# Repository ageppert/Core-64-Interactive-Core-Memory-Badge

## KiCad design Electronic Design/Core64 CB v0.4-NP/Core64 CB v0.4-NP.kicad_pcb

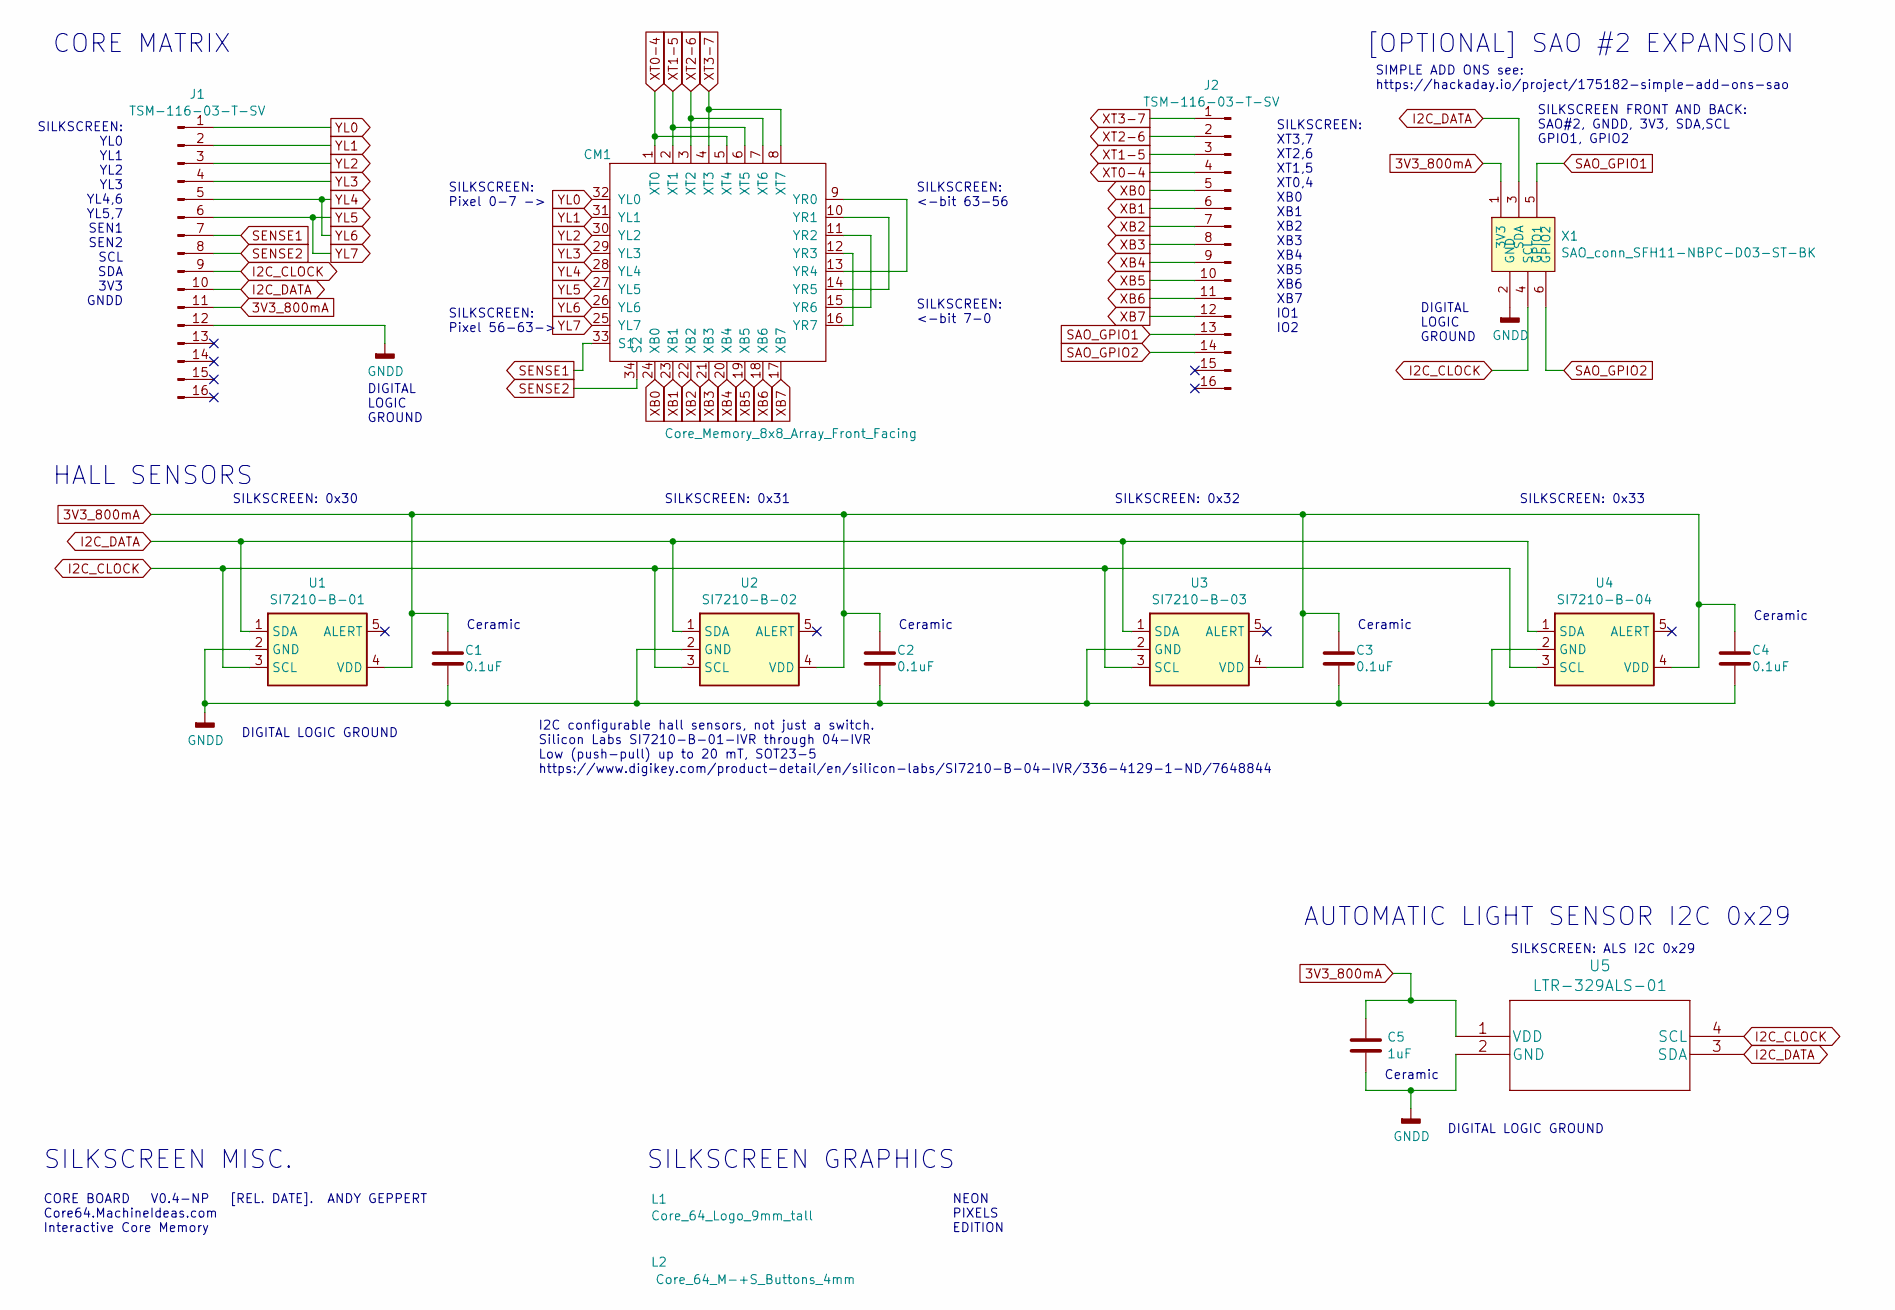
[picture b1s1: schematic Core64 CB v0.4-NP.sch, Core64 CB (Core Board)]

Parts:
C1, C2, C3, C4: 0.1uF; C_0805_2012Metric
C5: 1uF; C_0805_2012Metric
CM1: Core_Memory_8x8_Array_Front_Facing; core_64_0.3in_spacing_front_facing
J1, J2: TSM-116-03-T-SV‎; PinHeader_1x16_P2.54mm_Vertical
L1: Core_64_Logo_9mm_tall; Core64_Logo_9mm_tall
L2: Core_64_M-+S_Buttons_4mm; Core64-M_-_+_S_Buttons
U1: SI7210-B-01; SOT-23-5
U2: SI7210-B-02; SOT-23-5
U3: SI7210-B-03; SOT-23-5
U4: SI7210-B-04; SOT-23-5
U5: LTR-329ALS-01
X1: SAO_conn_SFH11-NBPC-D03-ST-BK; Badgelife-SAOv169-BADGE-2x3

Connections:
3V3_800mA: C1.1, C2.1, C3.1, C4.1, C5.1, J1.11, U1.4 (VDD), U2.4 (VDD), U3.4 (VDD), U4.4 (VDD), U5.1 (VDD), X1.1 (3V3)
GNDD: C1.2, C2.2, C3.2, C4.2, C5.2, J1.12, U1.2 (GND), U2.2 (GND), U3.2 (GND), U4.2 (GND), U5.2 (GND), X1.2 (GND)
I2C_CLOCK: J1.9, U1.3 (SCL), U2.3 (SCL), U3.3 (SCL), U4.3 (SCL), U5.4 (SCL), X1.4 (SCL)
I2C_DATA: J1.10, U1.1 (SDA), U2.1 (SDA), U3.1 (SDA), U4.1 (SDA), U5.3 (SDA), X1.3 (SDA)
unnamed: CM1.10 (YR1), CM1.14 (YR5)
unnamed: CM1.11 (YR2), CM1.15 (YR6)
unnamed: CM1.12 (YR3), CM1.16 (YR7)
unnamed: CM1.9 (YR0), CM1.13 (YR4)
SAO_GPIO1: J2.13, X1.5 (GPIO1)
SAO_GPIO2: J2.14, X1.6 (GPIO2)
SENSE1: CM1.33 (S1), J1.7
SENSE2: CM1.34 (S2), J1.8
XB0: CM1.24 (XB0), J2.5
XB1: CM1.23 (XB1), J2.6
XB2: CM1.22 (XB2), J2.7
XB3: CM1.21 (XB3), J2.8
XB4: CM1.20 (XB4), J2.9
XB5: CM1.19 (XB5), J2.10
XB6: CM1.18 (XB6), J2.11
XB7: CM1.17 (XB7), J2.12
XT0-4: CM1.1 (XT0), CM1.5 (XT4), J2.4
XT1-5: CM1.2 (XT1), CM1.6 (XT5), J2.3
XT2-6: CM1.3 (XT2), CM1.7 (XT6), J2.2
XT3-7: CM1.4 (XT3), CM1.8 (XT7), J2.1
YL0: CM1.32 (YL0), J1.1
YL1: CM1.31 (YL1), J1.2
YL2: CM1.30 (YL2), J1.3
YL3: CM1.29 (YL3), J1.4
YL4: CM1.26 (YL6), CM1.28 (YL4), J1.5
YL5: CM1.25 (YL7), CM1.27 (YL5), J1.6

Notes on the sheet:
SILKSCREEN: YL0 YL1 YL2 YL3 YL4,6 YL5,7 SEN1 SEN2 SCL SDA 3V3 GNDD
SILKSCREEN: XT3,7 XT2,6 XT1,5 XT0,4 XB0 XB1 XB2 XB3 XB4 XB5 XB6 XB7 IO1 IO2
DIGITAL LOGIC GROUND
I2C configurable hall sensors, not just a switch. Silicon Labs SI7210-B-01-IVR through 04-IVR Low (push-pull) up to 20 mT, SOT23-5 https://www.digikey.com/product-detail/en/silicon-labs/SI7210-B-04-IVR/336-4129-1-ND/7648844
DIGITAL LOGIC GROUND
SILKSCREEN: ALS I2C 0x29
SILKSCREEN FRONT AND BACK: SAO#2, GNDD, 3V3, SDA,SCL GPIO1, GPIO2
AUTOMATIC LIGHT SENSOR I2C 0x29
SILKSCREEN GRAPHICS
HALL SENSORS
CORE MATRIX
[OPTIONAL] SAO #2 EXPANSION
SILKSCREEN: 0x30
SILKSCREEN: 0x31
SILKSCREEN: 0x32
SILKSCREEN: 0x33
Ceramic
SILKSCREEN: Pixel 0-7 ->
SILKSCREEN: <-bit 63-56
SILKSCREEN: <-bit 7-0
SILKSCREEN: Pixel 56-63->
CORE BOARD V0.4-NP [REL. DATE]. ANDY GEPPERT Core64.MachineIdeas.com Interactive Core Memory
SILKSCREEN MISC.
NEON PIXELS EDITION
SIMPLE ADD ONS see: https://hackaday.io/project/175182-simple-add-ons-sao

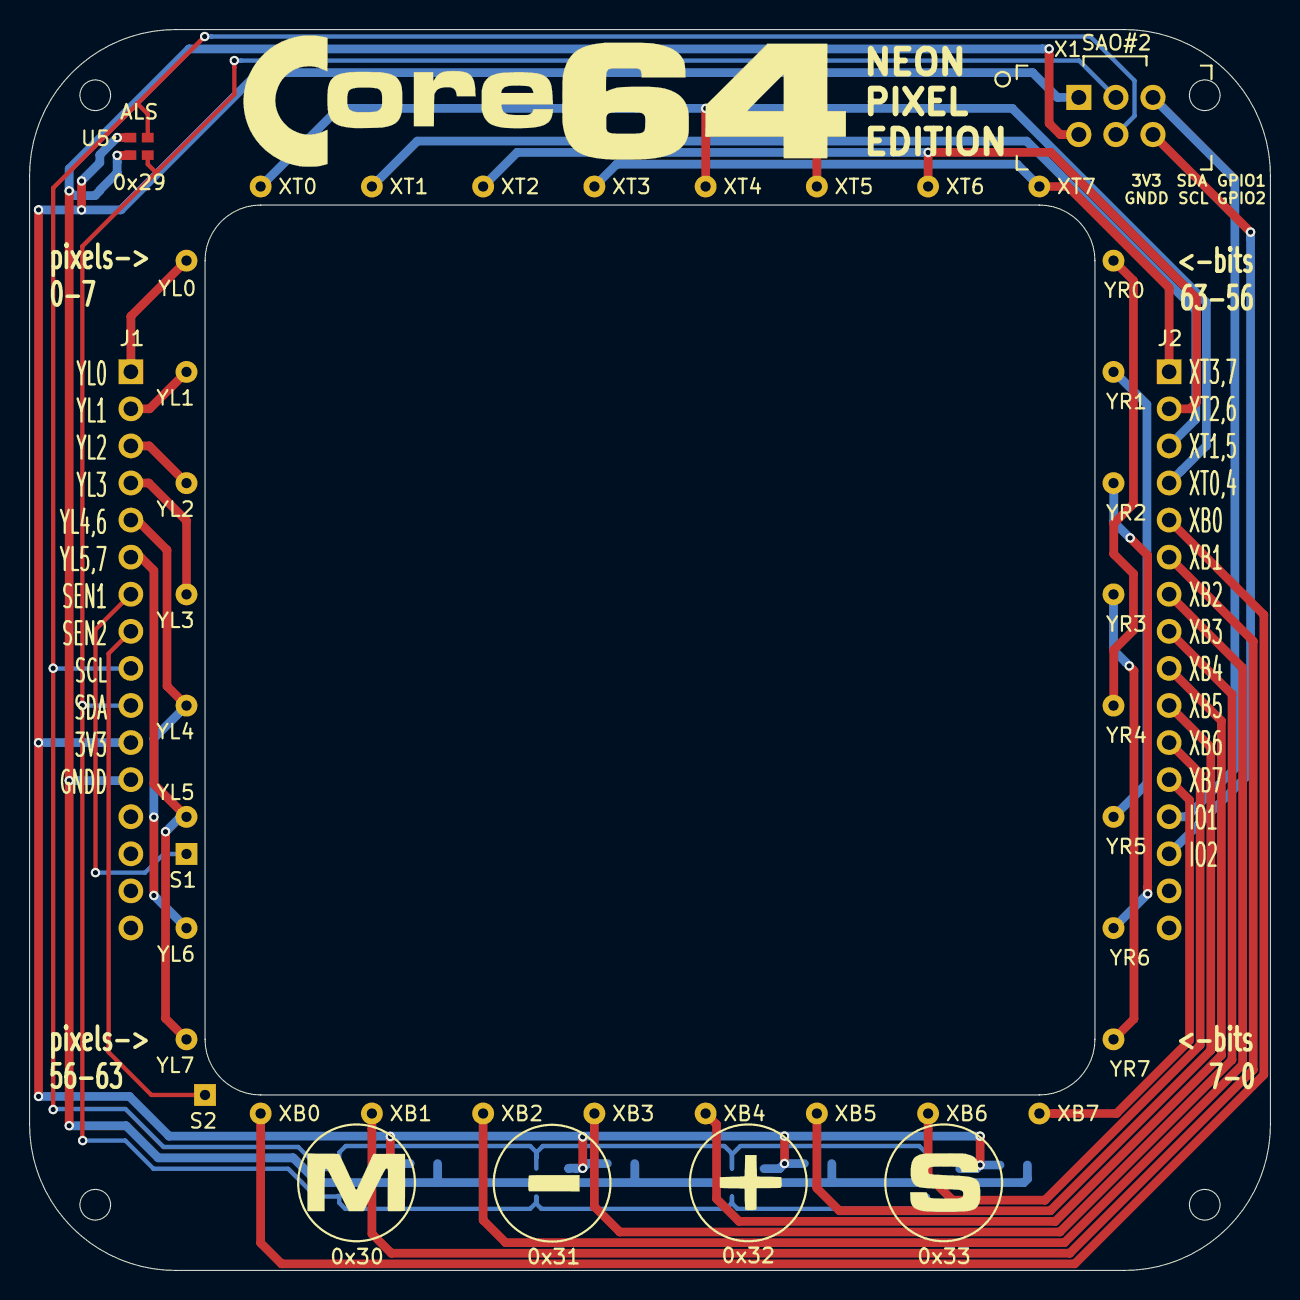
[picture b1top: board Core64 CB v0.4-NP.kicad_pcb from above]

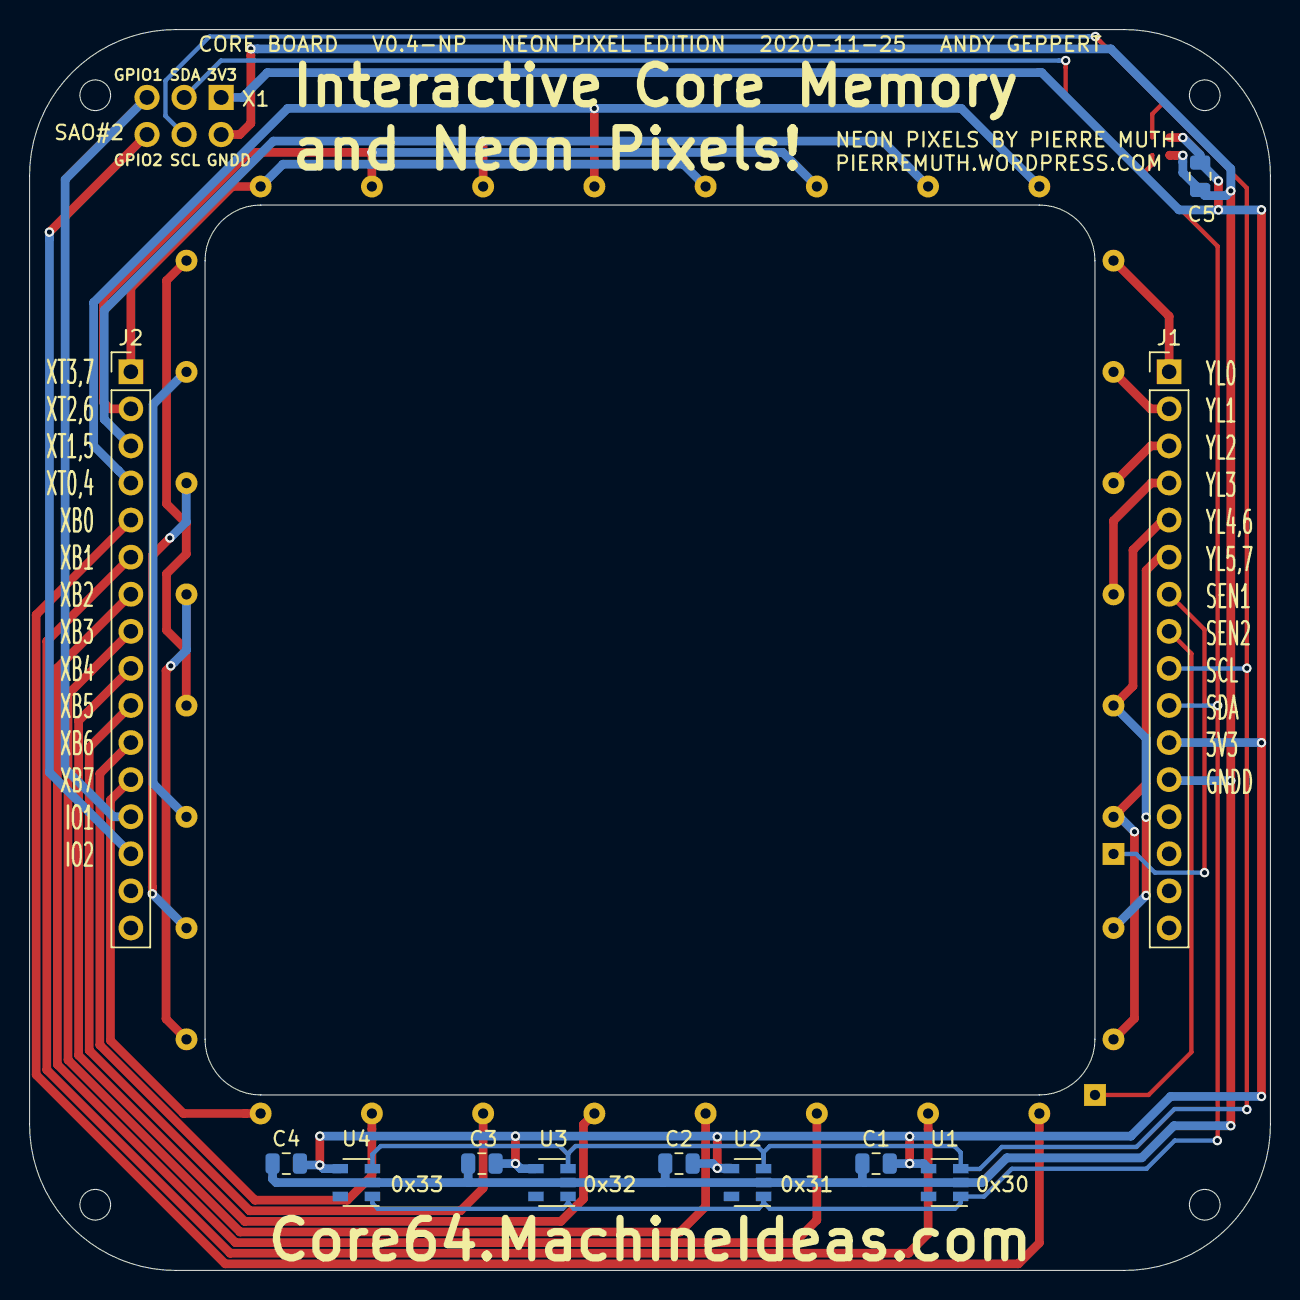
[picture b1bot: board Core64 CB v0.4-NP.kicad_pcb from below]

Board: 2 copper layers, 85.0 x 85.0 mm, 16 parts (11 on the bottom side), 30 nets.

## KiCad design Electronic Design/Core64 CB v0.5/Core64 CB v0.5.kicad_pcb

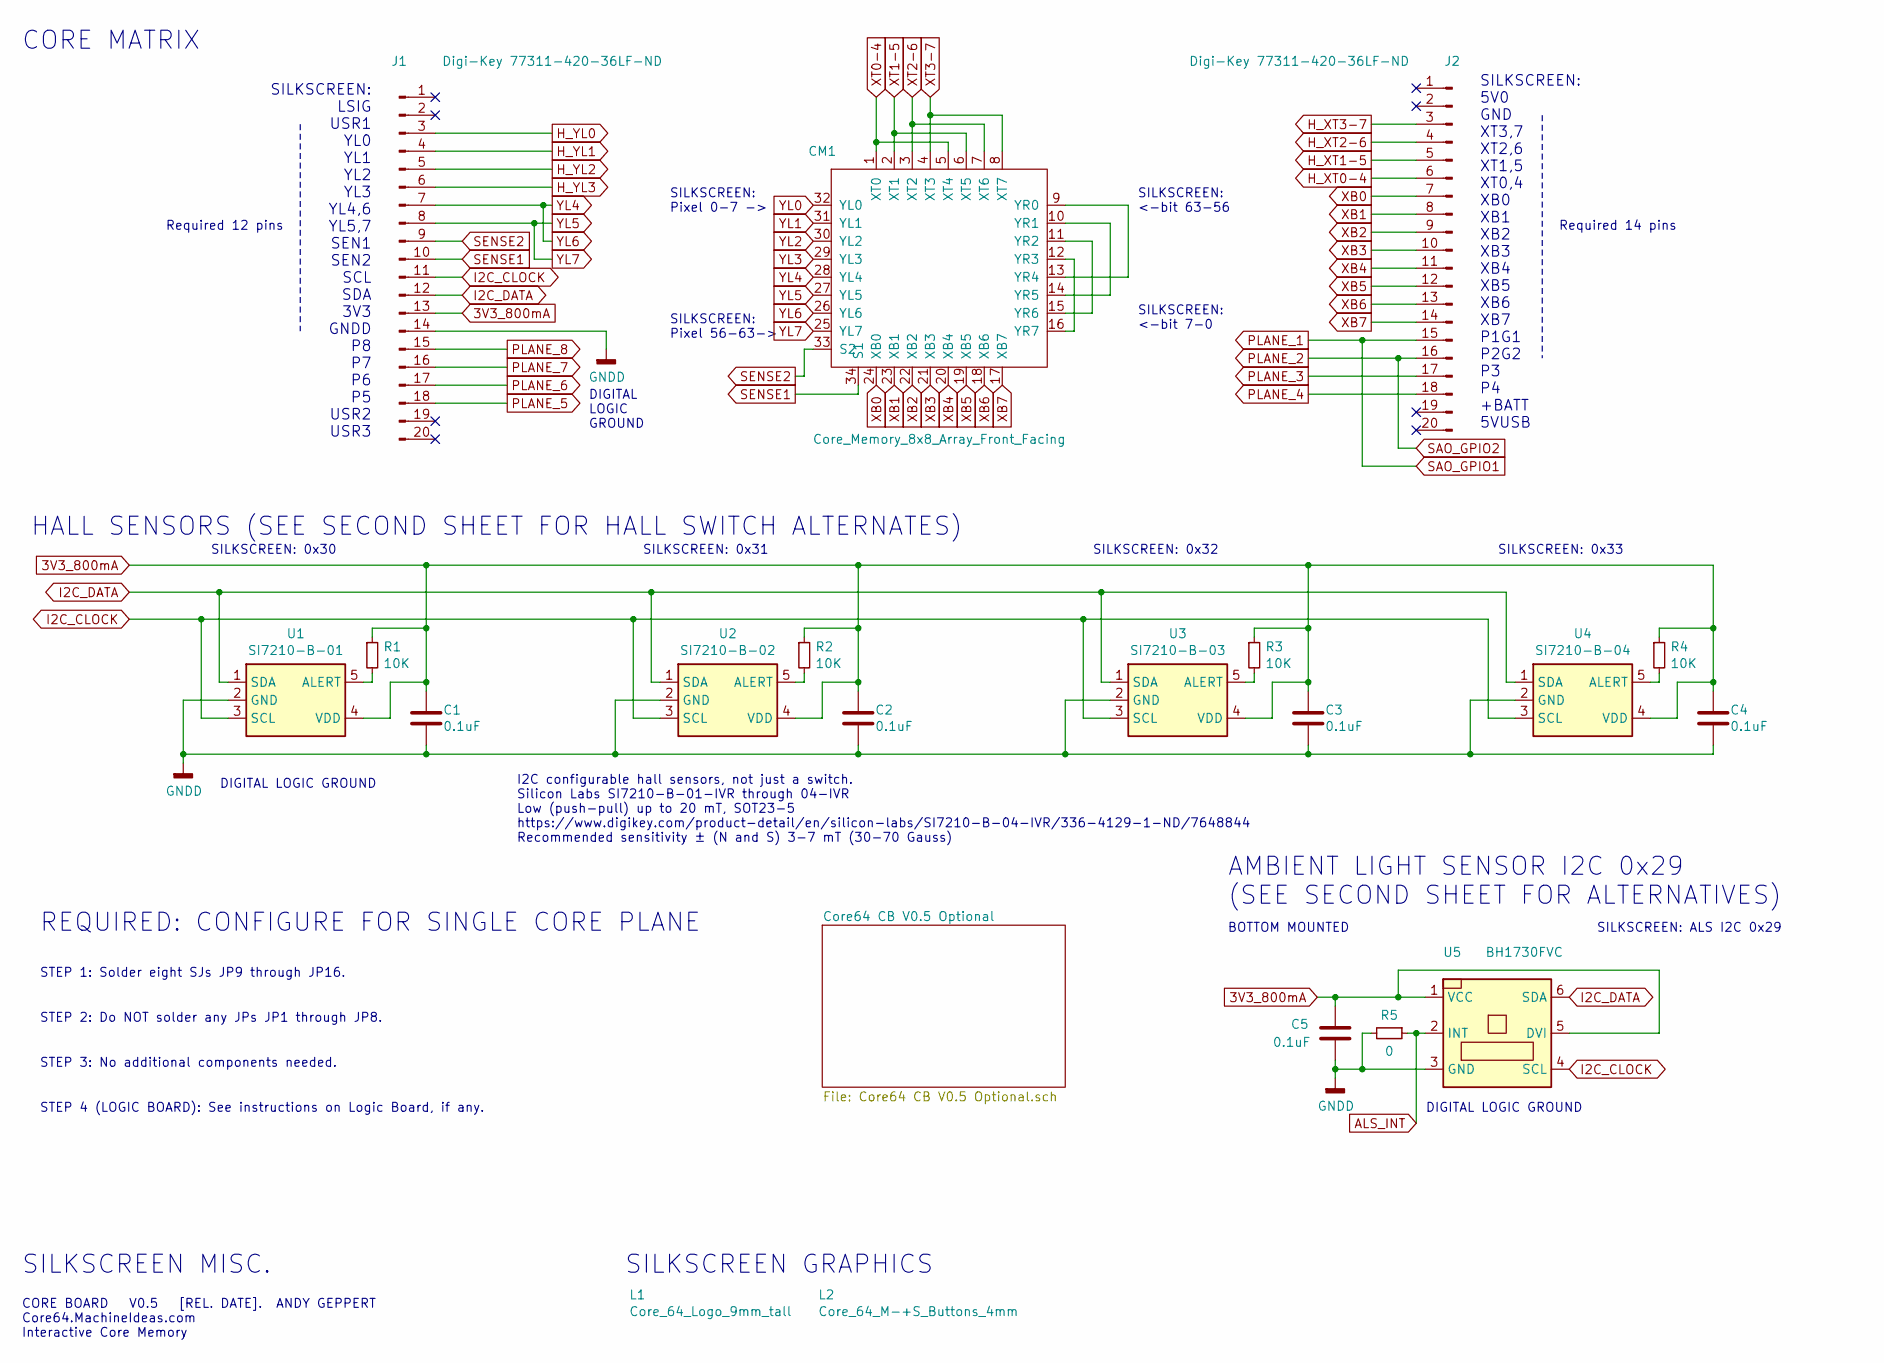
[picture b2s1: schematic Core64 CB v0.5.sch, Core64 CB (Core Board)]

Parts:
C1, C2, C3, C4, C5: 0.1uF; C_0805_2012Metric; LCSC C396718
CM1: Core_Memory_8x8_Array_Front_Facing; core_64_6.75mm_square_v0.5_front_facing
J1, J2: Digi-Key 77311-420-36LF-ND; PinHeader_1x20_P2.54mm_Vertical_SMD_and_TH_Pin1Right
L1: Core_64_Logo_9mm_tall; Core64_Logo_9mm_tall
L2: Core_64_M-+S_Buttons_4mm; Core64-M_-_+_S_Buttons
R1, R2, R3, R4: 10K; R_0805_2012Metric; LCSC C269724
R5: 0; R_0805_2012Metric; LCSC C115306
U1: SI7210-B-01; SOT-23-5
U2: SI7210-B-02; SOT-23-5
U3: SI7210-B-03; SOT-23-5
U4: SI7210-B-04; SOT-23-5
U5: BH1730FVC; BH1730-backside; LCSC C79616

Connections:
3V3_800mA: C1.1, C2.1, C3.1, C4.1, C5.1, J1.13, R1.1, R2.1, R3.1, R4.1, U1.4 (VDD), U2.4 (VDD), U3.4 (VDD), U4.4 (VDD), U5.1 (VCC), U5.5 (DVI); also elsewhere on the board
ALS_INT: R5.1, U5.2 (INT); also elsewhere on the board
GNDD: C1.2, C2.2, C3.2, C4.2, C5.2, J1.14, R5.2, U1.2 (GND), U2.2 (GND), U3.2 (GND), U4.2 (GND), U5.3 (GND); also elsewhere on the board
H_XT0-4: J2.6; also elsewhere on the board
H_XT1-5: J2.5; also elsewhere on the board
H_XT2-6: J2.4; also elsewhere on the board
H_XT3-7: J2.3; also elsewhere on the board
H_YL0: J1.3; also elsewhere on the board
H_YL1: J1.4; also elsewhere on the board
H_YL2: J1.5; also elsewhere on the board
H_YL3: J1.6; also elsewhere on the board
I2C_CLOCK: J1.11, U1.3 (SCL), U2.3 (SCL), U3.3 (SCL), U4.3 (SCL), U5.4 (SCL); also elsewhere on the board
I2C_DATA: J1.12, U1.1 (SDA), U2.1 (SDA), U3.1 (SDA), U4.1 (SDA), U5.6 (SDA); also elsewhere on the board
unnamed: CM1.10 (YR1), CM1.14 (YR5)
unnamed: CM1.11 (YR2), CM1.15 (YR6)
unnamed: CM1.12 (YR3), CM1.16 (YR7)
unnamed: CM1.9 (YR0), CM1.13 (YR4)
unnamed: R1.2, U1.5 (ALERT)
unnamed: R2.2, U2.5 (ALERT)
unnamed: R3.2, U3.5 (ALERT)
unnamed: R4.2, U4.5 (ALERT)
PLANE_1: J2.15; also elsewhere on the board
PLANE_2: J2.16; also elsewhere on the board
PLANE_3: J2.17; also elsewhere on the board
PLANE_4: J2.18; also elsewhere on the board
PLANE_5: J1.18; also elsewhere on the board
PLANE_6: J1.17; also elsewhere on the board
PLANE_7: J1.16; also elsewhere on the board
PLANE_8: J1.15; also elsewhere on the board
SENSE1: CM1.34 (S1), J1.10
SENSE2: CM1.33 (S2), J1.9
XB0: CM1.24 (XB0), J2.7
XB1: CM1.23 (XB1), J2.8
XB2: CM1.22 (XB2), J2.9
XB3: CM1.21 (XB3), J2.10
XB4: CM1.20 (XB4), J2.11
XB5: CM1.19 (XB5), J2.12
XB6: CM1.18 (XB6), J2.13
XB7: CM1.17 (XB7), J2.14
XT0-4: CM1.1 (XT0), CM1.5 (XT4); also elsewhere on the board
XT1-5: CM1.2 (XT1), CM1.6 (XT5); also elsewhere on the board
XT2-6: CM1.3 (XT2), CM1.7 (XT6); also elsewhere on the board
XT3-7: CM1.4 (XT3), CM1.8 (XT7); also elsewhere on the board
YL0: CM1.32 (YL0); also elsewhere on the board
YL1: CM1.31 (YL1); also elsewhere on the board
YL2: CM1.30 (YL2); also elsewhere on the board
YL3: CM1.29 (YL3); also elsewhere on the board
YL4: CM1.26 (YL6), CM1.28 (YL4), J1.7
YL5: CM1.25 (YL7), CM1.27 (YL5), J1.8

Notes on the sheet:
SILKSCREEN: LSIG USR1 YL0 YL1 YL2 YL3 YL4,6 YL5,7 SEN1 SEN2 SCL SDA 3V3 GNDD P8 P7 P6 P5 USR2 USR3
DIGITAL LOGIC GROUND
I2C configurable hall sensors, not just a switch. Silicon Labs SI7210-B-01-IVR through 04-IVR Low (push-pull) up to 20 mT, SOT23-5 https://www.digikey.com/product-detail/en/silicon-labs/SI7210-B-04-IVR/336-4129-1-ND/7648844 Recommended sensitivity ± (N and S) 3-7 mT (30-70 Gauss)
DIGITAL LOGIC GROUND
SILKSCREEN: ALS I2C 0x29
AMBIENT LIGHT SENSOR I2C 0x29 (SEE SECOND SHEET FOR ALTERNATIVES)
SILKSCREEN GRAPHICS
HALL SENSORS (SEE SECOND SHEET FOR HALL SWITCH ALTERNATES)
CORE MATRIX
SILKSCREEN: 0x30
SILKSCREEN: 0x31
SILKSCREEN: 0x32
SILKSCREEN: 0x33
SILKSCREEN: Pixel 0-7 ->
SILKSCREEN: <-bit 63-56
SILKSCREEN: <-bit 7-0
SILKSCREEN: Pixel 56-63->
CORE BOARD V0.5 [REL. DATE]. ANDY GEPPERT Core64.MachineIdeas.com Interactive Core Memory
SILKSCREEN MISC.
REQUIRED: CONFIGURE FOR SINGLE CORE PLANE
STEP 1: Solder eight SJs JP9 through JP16.
STEP 2: Do NOT solder any JPs JP1 through JP8.
STEP 3: No additional components needed.
STEP 4 (LOGIC BOARD): See instructions on Logic Board, if any.
Required 14 pins
SILKSCREEN: 5V0 GND XT3,7 XT2,6 XT1,5 XT0,4 XB0 XB1 XB2 XB3 XB4 XB5 XB6 XB7 P1G1 P2G2 P3 P4 +BATT 5VUSB
Required 12 pins
BOTTOM MOUNTED

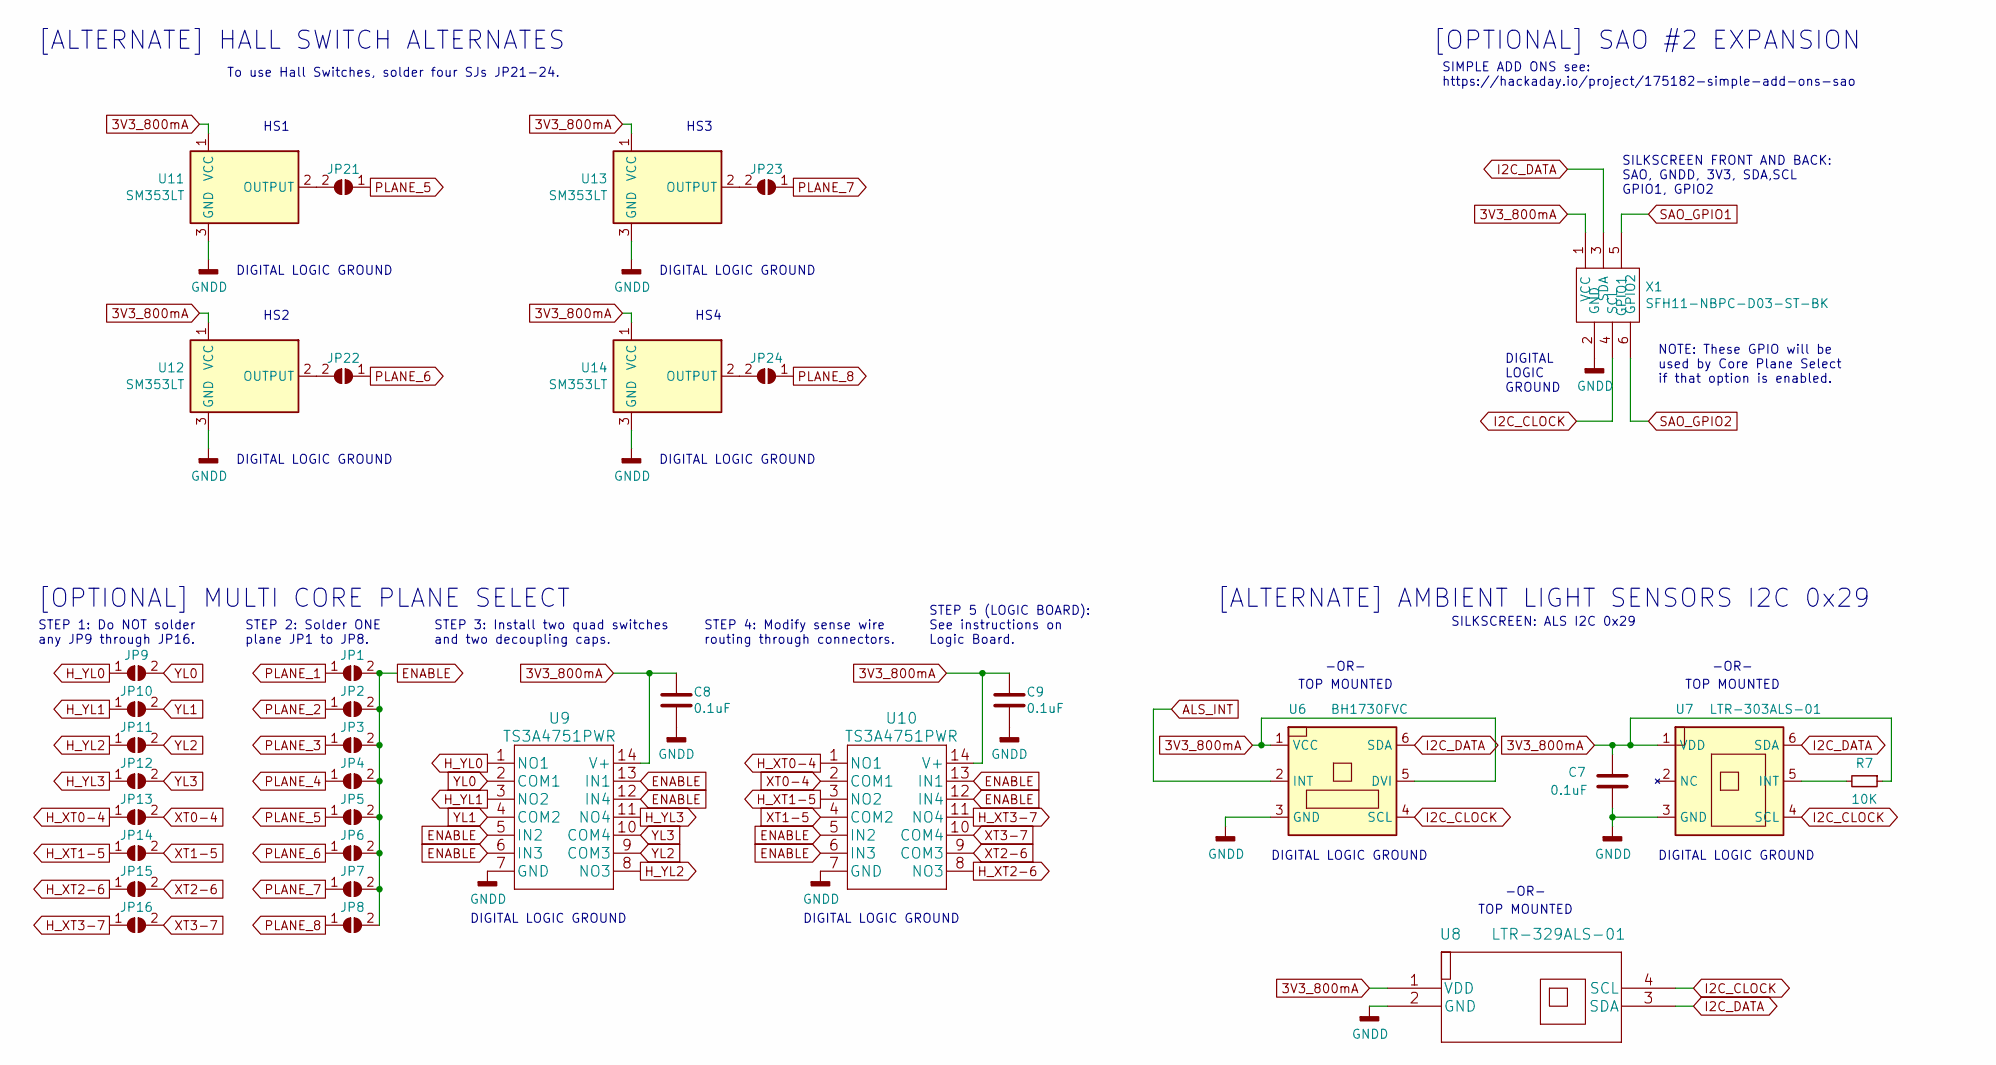
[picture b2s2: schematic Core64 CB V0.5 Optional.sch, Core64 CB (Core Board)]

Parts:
C7, C8, C9: 0.1uF; C_0805_2012Metric
JP1, JP2, JP3, JP4, JP5, JP6, JP7, JP8, JP21, JP22, JP23, JP24: SolderJumper_2_Open; SolderJumper-2_P1.3mm_Open_Pad1.0x1.5mm
JP9, JP10, JP11, JP12, JP13, JP14, JP15, JP16: SolderJumper_2_Bridged; SolderJumper-2_P1.3mm_Open_Pad1.0x1.5mm
R7: 10K; R_0805_2012Metric; LCSC C269724
U6: BH1730FVC; REG_BD00IC0WHFV-GTR
U7: LTR-303ALS-01; Lite-On_LTR-303ALS-01; LCSC C364577
U8: LTR-329ALS-01
U9, U10: TS3A4751PWR
U11, U12, U13, U14: SM353LT; SOT-23
X1: SFH11-NBPC-D03-ST-BK; Badgelife-SAOv169-BADGE-2x3

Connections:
3V3_800mA: C7.1, C8.1, C9.1, R7.1, U6.1 (VCC), U6.5 (DVI), U7.1 (VDD), U8.1 (VDD), U9.14 (V+), U10.14 (V+), U11.1 (VCC), U12.1 (VCC), U13.1 (VCC), U14.1 (VCC), X1.1 (VCC); also elsewhere on the board
ALS_INT: U6.2 (INT); also elsewhere on the board
ENABLE: JP1.2 (B), JP2.2 (B), JP3.2 (B), JP4.2 (B), JP5.2 (B), JP6.2 (B), JP7.2 (B), JP8.2 (B), U9.5 (IN2), U9.6 (IN3), U9.12 (IN4), U9.13 (IN1), U10.5 (IN2), U10.6 (IN3), U10.12 (IN4), U10.13 (IN1)
GNDD: C7.2, C8.2, C9.2, U6.3 (GND), U7.3 (GND), U8.2 (GND), U9.7 (GND), U10.7 (GND), U11.3 (GND), U12.3 (GND), U13.3 (GND), U14.3 (GND), X1.2 (GND); also elsewhere on the board
H_XT0-4: JP13.1 (A), U10.1 (NO1); also elsewhere on the board
H_XT1-5: JP14.1 (A), U10.3 (NO2); also elsewhere on the board
H_XT2-6: JP15.1 (A), U10.8 (NO3); also elsewhere on the board
H_XT3-7: JP16.1 (A), U10.11 (NO4); also elsewhere on the board
H_YL0: JP9.1 (A), U9.1 (NO1); also elsewhere on the board
H_YL1: JP10.1 (A), U9.3 (NO2); also elsewhere on the board
H_YL2: JP11.1 (A), U9.8 (NO3); also elsewhere on the board
H_YL3: JP12.1 (A), U9.11 (NO4); also elsewhere on the board
I2C_CLOCK: U6.4 (SCL), U7.4 (SCL), U8.4 (SCL), X1.4 (SCL); also elsewhere on the board
I2C_DATA: U6.6 (SDA), U7.6 (SDA), U8.3 (SDA), X1.3 (SDA); also elsewhere on the board
unnamed: JP21.2 (B), U11.2 (OUTPUT)
unnamed: JP22.2 (B), U12.2 (OUTPUT)
unnamed: JP23.2 (B), U13.2 (OUTPUT)
unnamed: JP24.2 (B), U14.2 (OUTPUT)
unnamed: R7.2, U7.5 (INT)
PLANE_1: JP1.1 (A), X1.5 (GPIO1); also elsewhere on the board
PLANE_2: JP2.1 (A), X1.6 (GPIO2); also elsewhere on the board
PLANE_3: JP3.1 (A); also elsewhere on the board
PLANE_4: JP4.1 (A); also elsewhere on the board
PLANE_5: JP5.1 (A), JP21.1 (A); also elsewhere on the board
PLANE_6: JP6.1 (A), JP22.1 (A); also elsewhere on the board
PLANE_7: JP7.1 (A), JP23.1 (A); also elsewhere on the board
PLANE_8: JP8.1 (A), JP24.1 (A); also elsewhere on the board
XT0-4: JP13.2 (B), U10.2 (COM1); also elsewhere on the board
XT1-5: JP14.2 (B), U10.4 (COM2); also elsewhere on the board
XT2-6: JP15.2 (B), U10.9 (COM3); also elsewhere on the board
XT3-7: JP16.2 (B), U10.10 (COM4); also elsewhere on the board
YL0: JP9.2 (B), U9.2 (COM1); also elsewhere on the board
YL1: JP10.2 (B), U9.4 (COM2); also elsewhere on the board
YL2: JP11.2 (B), U9.9 (COM3); also elsewhere on the board
YL3: JP12.2 (B), U9.10 (COM4); also elsewhere on the board

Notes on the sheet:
DIGITAL LOGIC GROUND
-OR-
SILKSCREEN: ALS I2C 0x29
[ALTERNATE] AMBIENT LIGHT SENSORS I2C 0x29
[OPTIONAL] MULTI CORE PLANE SELECT
STEP 1: Do NOT solder any JP9 through JP16.
STEP 2: Solder ONE plane JP1 to JP8.
STEP 3: Install two quad switches and two decoupling caps.
STEP 4: Modify sense wire routing through connectors.
STEP 5 (LOGIC BOARD): See instructions on Logic Board.
SILKSCREEN FRONT AND BACK: SAO, GNDD, 3V3, SDA,SCL GPIO1, GPIO2
[OPTIONAL] SAO #2 EXPANSION
DIGITAL LOGIC GROUND
SIMPLE ADD ONS see: https://hackaday.io/project/175182-simple-add-ons-sao
NOTE: These GPIO will be used by Core Plane Select if that option is enabled.
[ALTERNATE] HALL SWITCH ALTERNATES
TOP MOUNTED
To use Hall Switches, solder four SJs JP21-24.
HS1
HS2
HS3
HS4

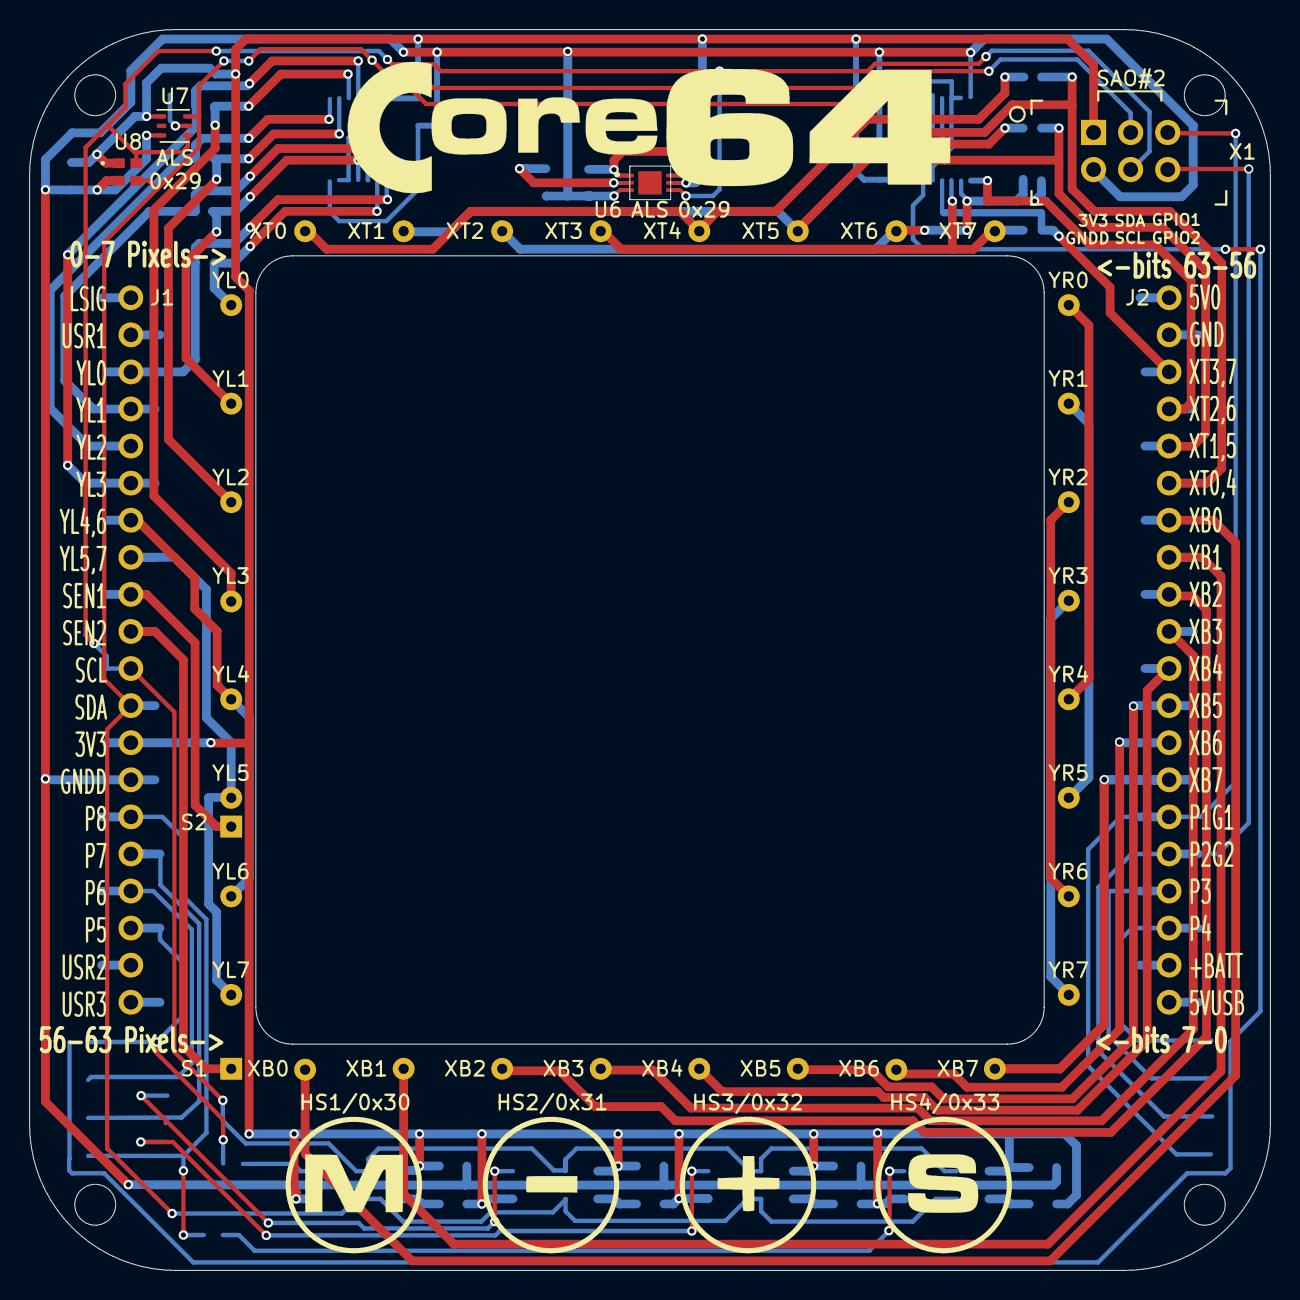
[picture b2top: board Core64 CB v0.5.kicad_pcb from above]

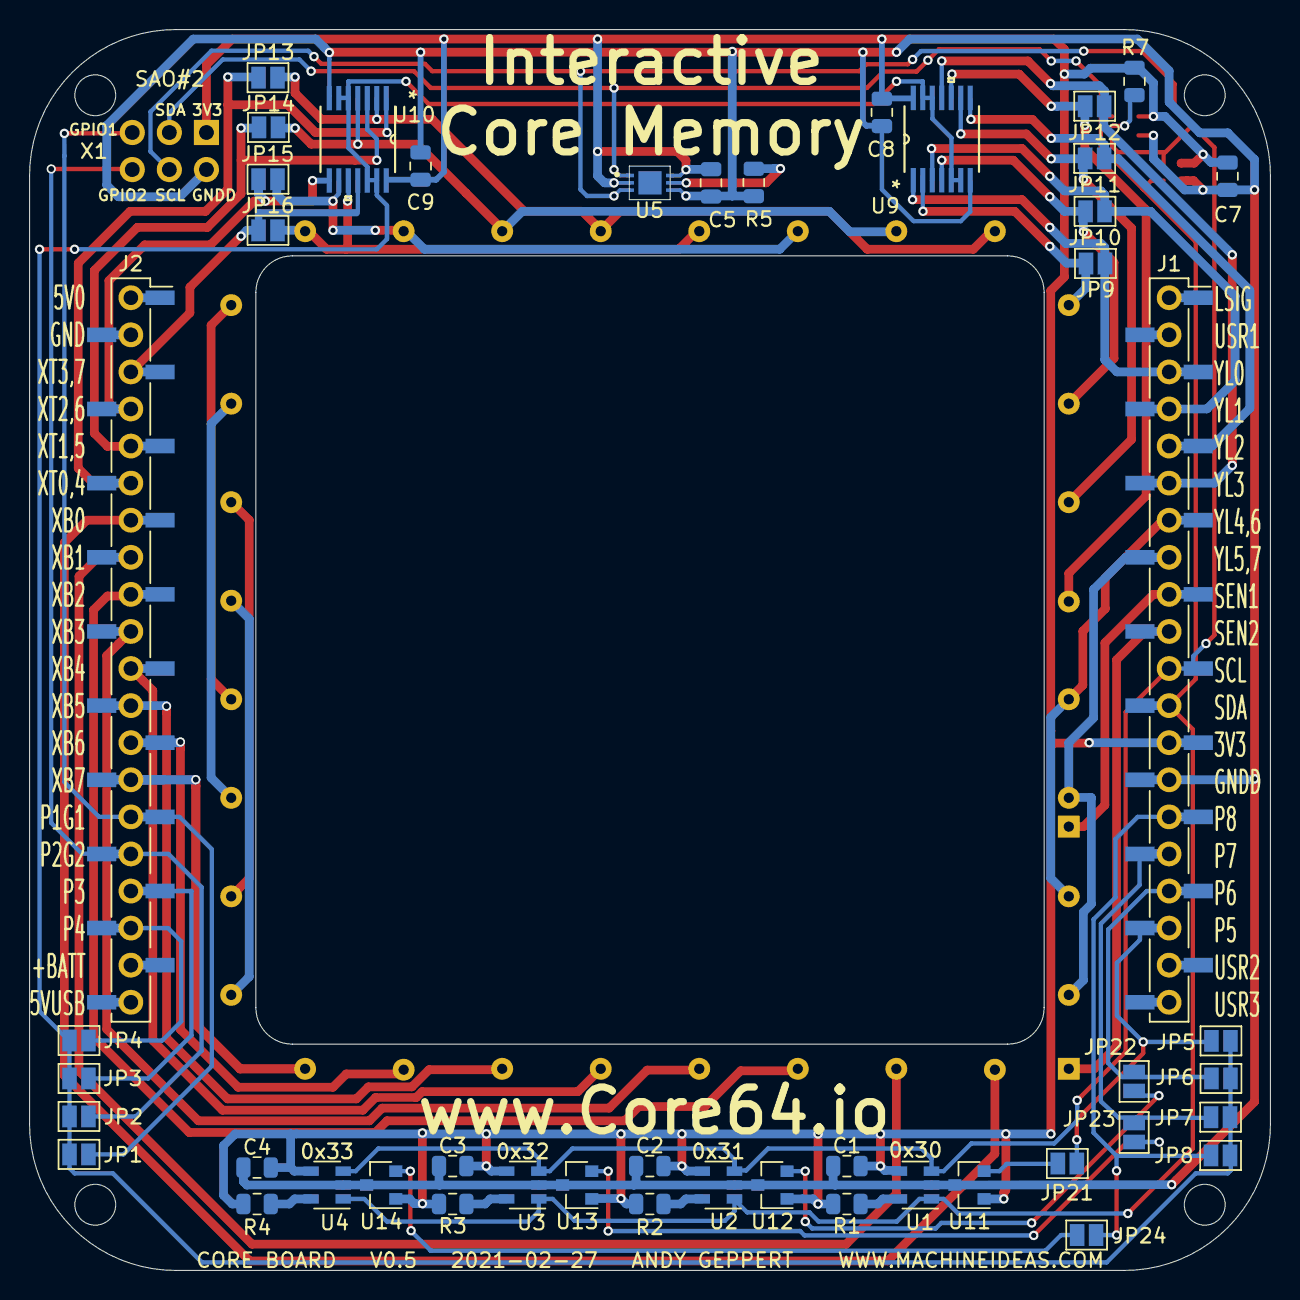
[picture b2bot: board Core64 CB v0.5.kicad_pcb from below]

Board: 2 copper layers, 85.0 x 85.0 mm, 54 parts (47 on the bottom side), 55 nets.

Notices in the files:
parts and their libraries:
Copyright 2016 Accelerated Designs. All rights reserved.
